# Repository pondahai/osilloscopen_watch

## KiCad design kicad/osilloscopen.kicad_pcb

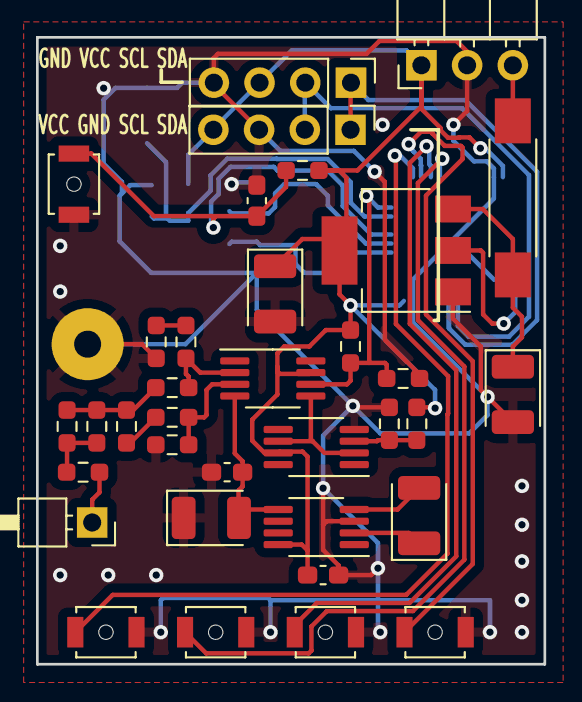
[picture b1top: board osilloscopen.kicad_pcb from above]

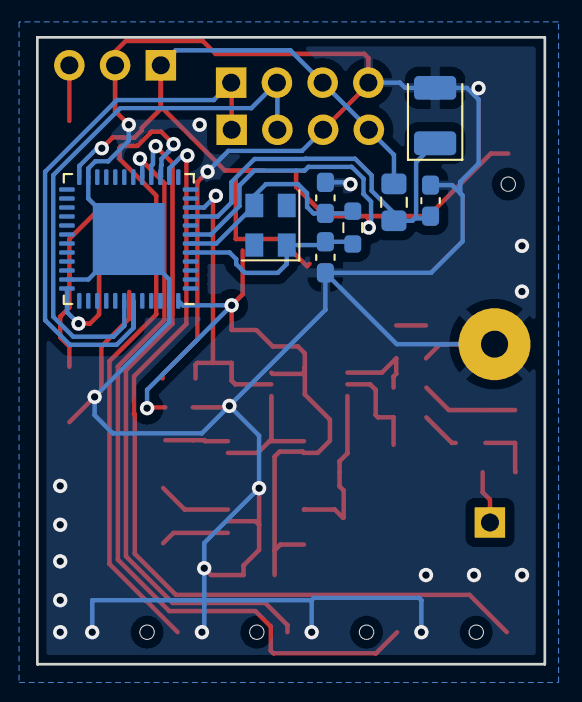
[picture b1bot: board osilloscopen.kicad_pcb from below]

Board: 2 copper layers, 28.2 x 34.8 mm, 48 parts (8 on the bottom side), 27 nets.

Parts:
C1, C2, C3, C8: 10u; CP_EIA-3528-21_Kemet-B
C4: 10n; C_0603_1608Metric_Pad1.08x0.95mm_HandSolder
C5, C6: 20p; C_0603_1608Metric_Pad1.08x0.95mm_HandSolder
C7: 100u; CP_EIA-3528-21_Kemet-B
C9, C10, C11: 100n; C_0603_1608Metric_Pad1.08x0.95mm_HandSolder
J2, J17: OLED; PinHeader_1x04_P2.54mm_Vertical
J3: tip; PinHeader_1x01_P2.54mm_Horizontal
J4: power; PinHeader_1x03_P2.54mm_Horizontal
J18: GND; SolderWirePad_1x01_Drill1.5mm
L1: 47u; L_0805_2012Metric_Pad1.15x1.40mm_HandSolder
MH1, MH2, MH3, MH4: MountingHole; MountingHole_3.5mm
R1: 3M; R_0603_1608Metric_Pad0.98x0.95mm_HandSolder
R2, R3, R4, R5, R6, R7, R8, R9, R13: 1M; R_0603_1608Metric_Pad0.98x0.95mm_HandSolder
R10, R11, R12: 1k; R_0603_1608Metric_Pad0.98x0.95mm_HandSolder
R14: n/a; R_0603_1608Metric_Pad0.98x0.95mm_HandSolder
R15: 10k; R_0603_1608Metric_Pad0.98x0.95mm_HandSolder
SW1, SW2, SW3, SW4: SW_Push; SW_SPST_B3U-1000P-B
SW5: POWER; SW_SPST_REED_CT05-XXXX-G1
SW6: RESET; SW_SPST_B3U-1000P-B
U1: AD623AN; MSOP-8_3x3mm_P0.65mm
U2: ICL7660; MSOP-8_3x3mm_P0.65mm
U3: STM32F103C6Ux; QFN-48-1EP_7x7mm_P0.5mm_EP5.6x5.6mm
U4: AP1117-33; SOT-223-3_TabPin2
U5: XXX; MSOP-8_3x3mm_P0.65mm
Y1: 8MHz; Crystal_SMD_EuroQuartz_MT-4Pin_3.2x2.5mm

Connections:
+5V: C8.1, SW5.2 (B), U4.3 (VI)
-3V3: C1.2, C10.1, U1.4 (Vs-), U2.5 (VOUT)
/KEY1: SW1.1, U3.14 (PA4)
/KEY2: SW2.1, U3.15 (PA5)
/KEY3: SW3.1, U3.16 (PA6)
/KEY4: SW4.1, U3.17 (PA7)
/RESET#: C11.1, R15.2, SW6.1, U3.7 (NRST)
/SCL: J2.2, J17.2, U3.42 (PB6)
/SDA: J2.1, J17.1, U3.43 (PB7)
/VDDA: C3.1, C4.1, L1.1, U3.9 (VDDA)
GNDREF: C1.1, C3.2, C4.2, C5.1, C6.1, C7.2, C8.2, C9.2, C10.2, C11.2, J2.3, J4.2, J17.4, J18.1, R6.1, R9.1, R11.1, R12.1, SW1.2, SW2.2, SW3.2, SW4.2, SW6.2, U2.3 (GND), U3.23 (VSS), U3.35 (VSS), U3.47 (VSS), U3.49 (VSS), U4.1 (GND), U5.4 (V-)
unnamed: C2.1, U2.2 (CAP+)
unnamed: C2.2, U2.4 (CAP-)
unnamed: C5.2, R13.1, U3.5 (PD0), Y1.1
unnamed: C6.2, R13.2, U3.6 (PD1), Y1.3
unnamed: J3.1, R1.2
unnamed: J4.3, SW5.1 (A)
unnamed: R1.1, R2.2, R3.2
unnamed: R2.1, R3.1, R4.2, R7.2
unnamed: R4.1, R5.2
unnamed: R5.1, R6.2, U1.3 (+)
unnamed: R7.1, R8.2, U1.2 (-)
unnamed: R8.1, R9.2
unnamed: R10.1, R11.2, U5.3 (+)
unnamed: R12.2, R14.2, U1.6, U3.10 (PA0)
unnamed: U1.5 (Ref), U5.2 (-), U5.6
VDD: C7.1, C9.1, J2.4, J4.1, J17.3, L1.2, R10.2, R14.1, R15.1, U1.7 (Vs+), U2.8 (V+), U3.24 (VDD), U3.36 (VDD), U3.48 (VDD), U4.2 (VO), U5.7 (V+)

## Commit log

2022-02-17 layout complete
